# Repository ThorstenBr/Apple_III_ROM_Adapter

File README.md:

# Apple III ROM Adapter (B9 ROM)
* This project contains the design for an adpater for the Apple /// "**B9 ROM**" (the main system ROM to boot the 6502 CPU).
* Replaces the stock 4KB ROM with a programmable **27C64 EPROM or 28C64 EEPROM** (8KB).

The Apple /// supports two 4KB ROM banks, though the originally installed Apple /// ROM was only 4KB.

The option to install a custom ROM can be useful though. You can install a ROM variant providing additional features - such as bootstrapping from a (virtual) harddisk (ProDOS interface cards), or installing a ROM with an extended "debug monitor".

## Custom ROM Adapter
The PCB adapts the Apple ///'s pinout for a "2532" ROM to a more common 27c64/28c64 EPROM/EEPROM.
It also takes care of providing the necessary clearance.
The Apple ///'s "B9" ROM is located in a tight space directly below the keyboard.
Simple, generic ROM adapters will not fit in this restricted space.
This adapter was designed to move the top (E)PROM as far to the rear as possible (closer to the memory board). This provides the necessary clearance (since the keyboard slopes upwards towards the rear).

## Building the Adapter

### Schematics and KiCad Project
The [KiCad](KiCad/) folder contains the schematics and PCB project files, if you wished to adapt the design.

A [schematics PDF](KiCad/Apple_III_ROM_Adapter-Schematics.pdf) is also available.

### Gerber Files
Here is a [ZIP file containing the Gerber files](Gerber/Apple_III_ROM_Adapter-v2.0.zip) required to order PCBs.

I ordered mine using a slightly thinner PCB thickness than usual: 1.2mm (default is usually 1.6mm).
The cost was the same. And since the clearance in the Apple /// chassis is major concern, I went with the thinner variant.

This worked great. For this tiny PCB the 1.2mm is absolutely enough. It turned out, however, that the PCB design provides more than enough clearance anyway. So the thinner 1.2mm PCB wasn't essential.

### PCB Design
**Top side:**

**Bottom side:**

## Jumpers
The two jumpers allow to change the mapping of the EPROMs "Vpp" and "OE" pins.

* By default, the PCB connects VPP to GND...
* ... and "OE" and "CS" are connected.

**They are preconfigured on the PCB. Do not add solder!**

For custom use cases (if you know what you are doing) the PCB traces between these jumper pads can be cut with a knife - if you need other connections.

## Capacitor
You can install a tiny 100nF capacitor on the PCB. But it's optional.
But since the adapter results in a longer supply connections - you may want to add it for stabilisation.

## Pin Headers
**Do not use standard pin headers!** Standard pin headers cannot be plugged into an IC socket. It would not fit - or you would damage the socket.

Use precision pin headers with round and extra thin pins.
I used [this type](https://www.reichelt.de/de/en/pin-header-rm-2-54mm-straight-1-row-40-pin-w-p-952-12-040-1-p331061.html?&nbc=1) - with round 0.5mm thin pins.

I slightly shortened the pins (you can adjust them one by one before soldering). It wasn't really necessary in my case (see above: I have about 4mm clearance anyway). But depending on the type of PCB, EPROM and pin headers, you may want to adjust the pins.

**Pro tip: check the clearance of your setup (PCB/pin header/ROM) before soldering...**

## Installation
The adapter replaces the mainboard ROM in position B9. The PCB was designed to fit the tight space inside the Apple /// chassis - below the keyboard. A normal adapter which just plugs the ROM on top of the mainboard's IC socket wouldn't fit.

The PCB sits flush on top of the TTL IC in position C9 (74LS260). This is of no major concern.
The 74LS260 barely dissipates any heat, so this is one of the ICs where the blocked cooling is not going to be a factor.

Here's a look from the top - when the keyboard is removed. The adapter has about 4mm clearance to the chassis (when using an EEPROM).
It's probably a bit less (maybe 2mm clearance) when using an EPROM (since EPROMs are usually higher).

## ROM Variants
Have a look at [this project](https://github.com/ThorstenBr/Apple_III_Custom_ROM) - providing some Apple /// ROM variants with additional functionality.

For example, an Apple /// ROM with extended debug monitor - adding a disassembler:

## License
This project is released under the "Creative Commons Attribution 4.0 International Public License". See [LICENSE](LICENSE).

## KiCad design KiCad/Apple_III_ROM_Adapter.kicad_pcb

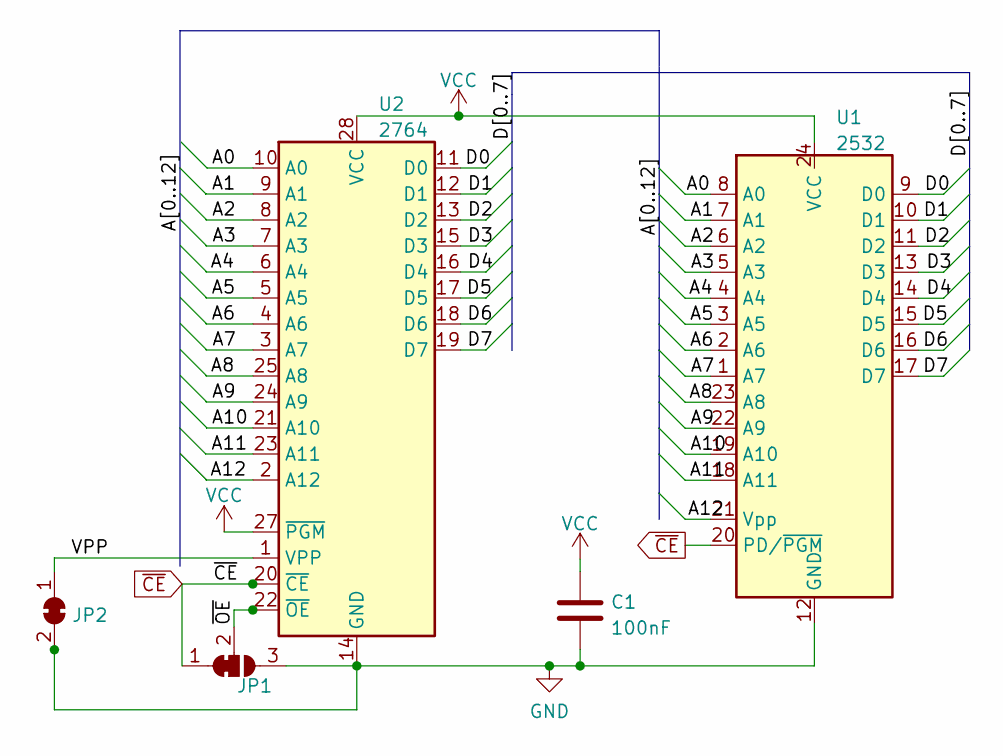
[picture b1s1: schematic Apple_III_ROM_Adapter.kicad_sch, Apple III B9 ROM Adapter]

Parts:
C1: 100nF; C_Disc_D4.3mm_W1.9mm_P5.00mm
JP1: SolderJumper_3_Bridged12; SolderJumper-3_P1.3mm_Bridged12_RoundedPad1.0x1.5mm_NumberL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
JP2: SolderJumper_2_Bridged; SolderJumper-2_P1.3mm_Bridged_RoundedPad1.0x1.5mm
U1: 2532; DIP-24_W15.24mm
U2: 2764; DIP-28_W15.24mm

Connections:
/A0: U1.8 (A0), U2.10 (A0)
/A1: U1.7 (A1), U2.9 (A1)
/A2: U1.6 (A2), U2.8 (A2)
/A3: U1.5 (A3), U2.7 (A3)
/A4: U1.4 (A4), U2.6 (A4)
/A5: U1.3 (A5), U2.5 (A5)
/A6: U1.2 (A6), U2.4 (A6)
/A7: U1.1 (A7), U2.3 (A7)
/A8: U1.23 (A8), U2.25 (A8)
/A9: U1.22 (A9), U2.24 (A9)
/A10: U1.19 (A10), U2.21 (A10)
/A11: U1.18 (A11), U2.23 (A11)
/A12: U1.21 (Vpp), U2.2 (A12)
/D0: U1.9 (D0), U2.11 (D0)
/D1: U1.10 (D1), U2.12 (D1)
/D2: U1.11 (D2), U2.13 (D2)
/D3: U1.13 (D3), U2.15 (D3)
/D4: U1.14 (D4), U2.16 (D4)
/D5: U1.15 (D5), U2.17 (D5)
/D6: U1.16 (D6), U2.18 (D6)
/D7: U1.17 (D7), U2.19 (D7)
/VPP: JP2.1 (A), U2.1 (VPP)
/~OE: JP1.2 (C), U2.22 (~OE)
GND: C1.2, JP1.3 (B), JP2.2 (B), U1.12 (GND), U2.14 (GND)
VCC: C1.1, U1.24 (VCC), U2.27 (~PGM), U2.28 (VCC)
~CE: JP1.1 (A), U1.20 (PD/~PGM), U2.20 (~CE)

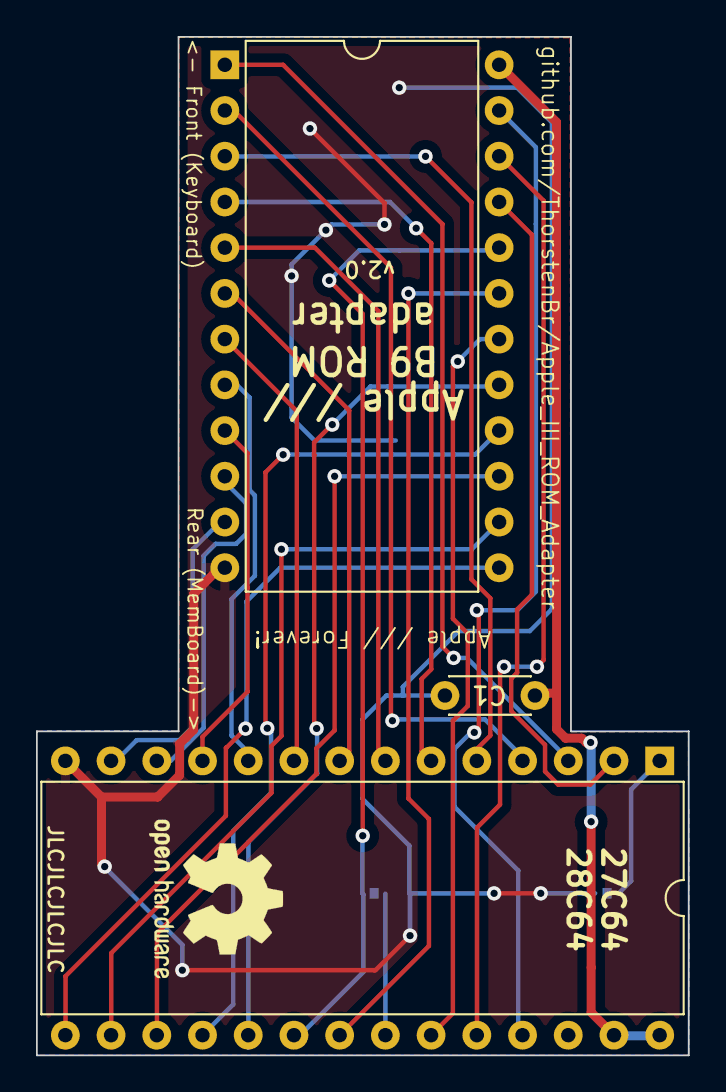
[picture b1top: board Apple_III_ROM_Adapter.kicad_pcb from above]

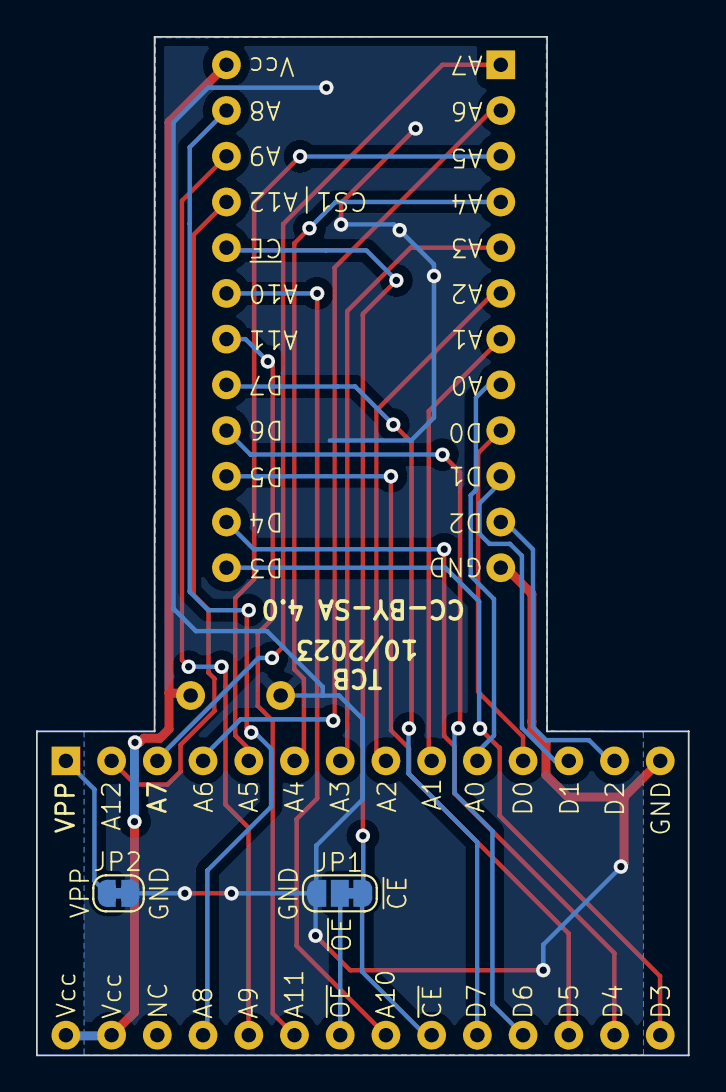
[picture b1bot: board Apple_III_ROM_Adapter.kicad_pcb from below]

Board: 2 copper layers, 36.2 x 56.6 mm, 5 parts (2 on the bottom side), 26 nets.

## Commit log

2023-08-27 Apple /// ROM adapter: v1.0.
2023-09-17 Added "work-in-progress" warning...
2023-10-14 New PCB design, v2.0 EPROM rotated by 90 degrees, moved all the way back to align with the memory sandwich board.
2023-10-14 Updated schematics, Gerber files and PCB images for v2.0.
2023-10-27 Removed WIP warning.
2023-10-27 Updated project description. Added photos.

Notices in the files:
KiCad/Apple_III_ROM_Adapter.kicad_pcb:
CC-BY-SA 4.0
